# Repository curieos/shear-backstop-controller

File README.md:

# Shear Backstop Controller
A shear backstop controller running on a Teensy 3.5 with AMIS30543 stepper drivers and an Adafruit TFT LCD

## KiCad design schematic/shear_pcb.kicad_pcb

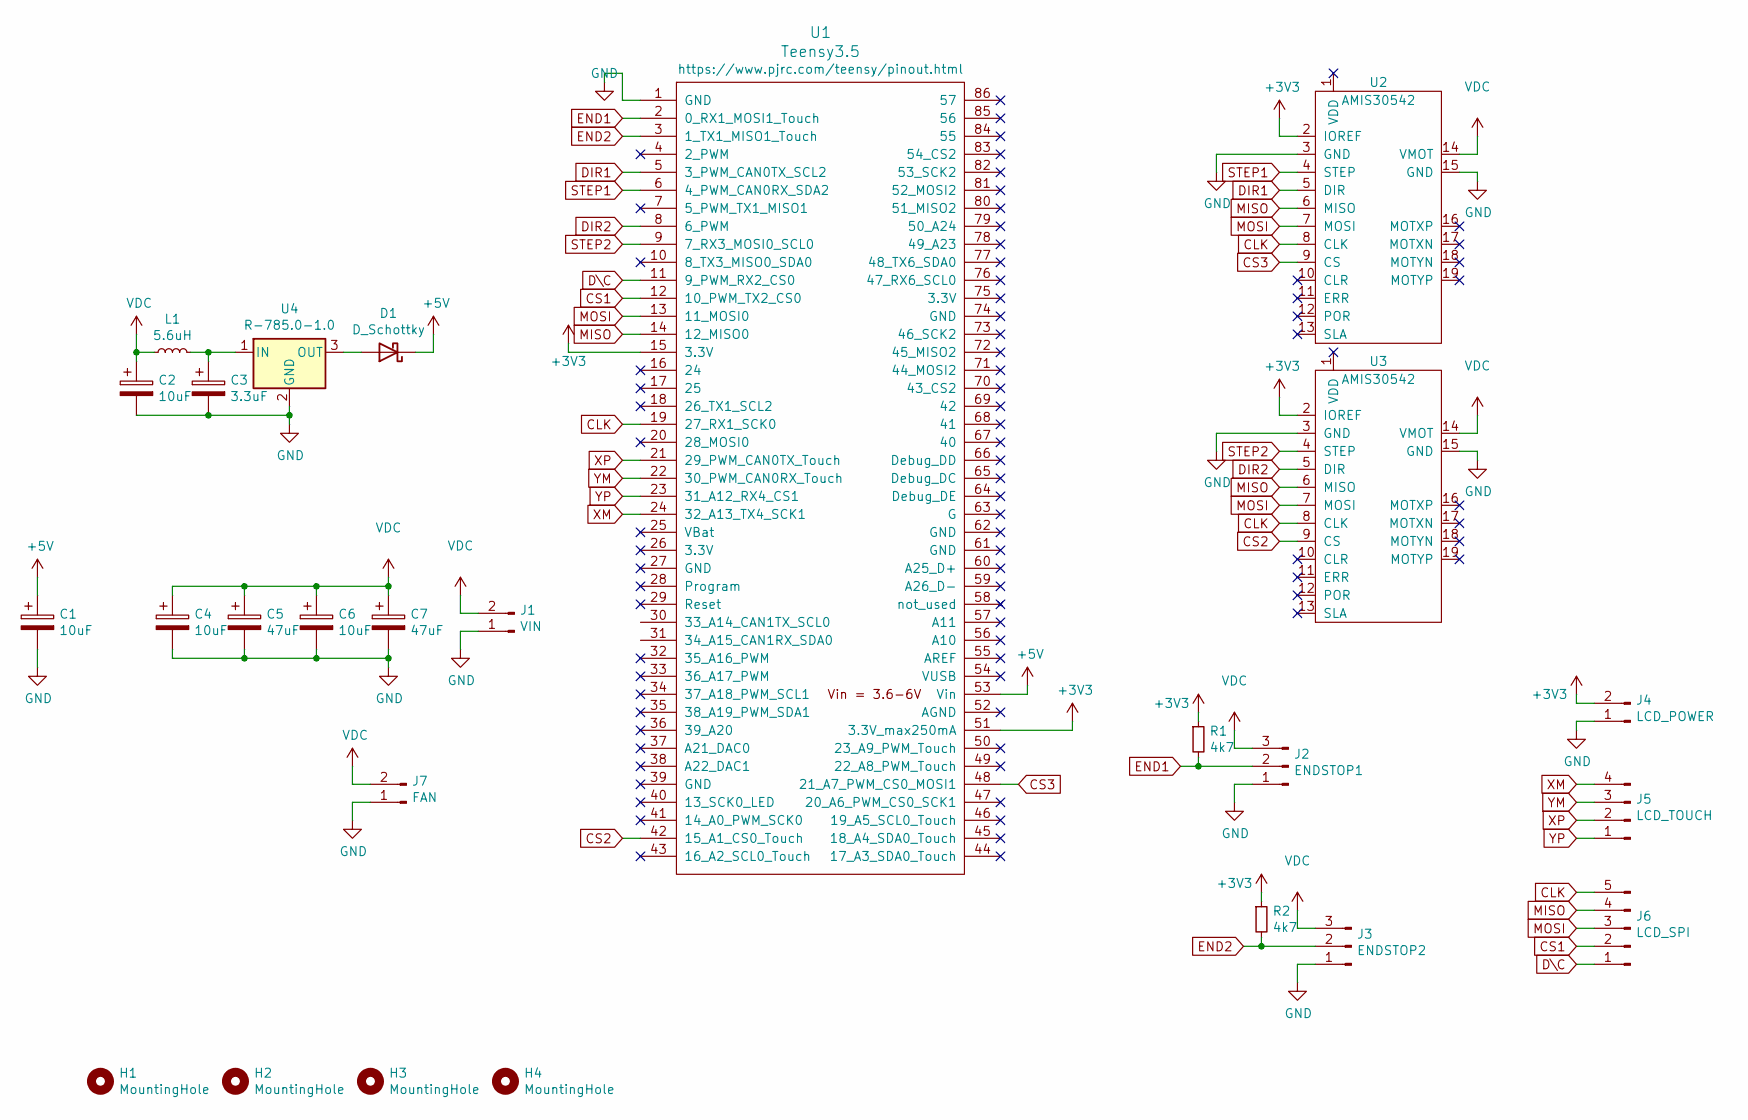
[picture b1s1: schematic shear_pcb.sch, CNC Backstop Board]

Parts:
C1: 10uF; C_1206_3216Metric_Pad1.42x1.75mm_HandSolder
C2: 10uF; C_1210_3225Metric_Pad1.42x2.65mm_HandSolder
C3: 3.3uF; C_1210_3225Metric_Pad1.42x2.65mm_HandSolder
C4, C6: 10uF; CP_Elec_6.3x3
C5, C7: 47uF; CP_Elec_6.3x3
D1: D_Schottky; D_0805_2012Metric_Pad1.15x1.40mm_HandSolder
H1, H2, H3, H4: MountingHole; MountingHole_3.2mm_M3_ISO7380
J1: VIN; TerminalBlock_bornier-2_P5.08mm
J2: ENDSTOP1; PinHeader_1x03_P2.54mm_Vertical
J3: ENDSTOP2; PinHeader_1x03_P2.54mm_Vertical
J4: LCD_POWER; PinHeader_1x02_P2.54mm_Vertical
J5: LCD_TOUCH; PinHeader_1x04_P2.54mm_Vertical
J6: LCD_SPI; PinHeader_1x05_P2.54mm_Vertical
J7: FAN; JST_EH_B2B-EH-A_1x02_P2.50mm_Vertical
L1: 5.6uH; L_Bourns-SRN4018
R1, R2: 4k7; R_0805_2012Metric_Pad1.15x1.40mm_HandSolder
U1: Teensy3.5; Teensy35_36
U2, U3: AMIS30542
U4: R-785.0-1.0; Converter_DCDC_RECOM_R-78E-0.5_THT

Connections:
+3V3: J4.2, R1.1, R2.1, U1.15 (3.3V), U1.51 (3.3V_max250mA), U2.2 (IOREF), U3.2 (IOREF)
+5V: C1.1, D1.1 (K), U1.53 (Vin)
CLK: J6.5, U1.19 (27_RX1_SCK0), U2.8 (CLK), U3.8 (CLK)
CS1: J6.2, U1.12 (10_PWM_TX2_CS0)
CS2: U1.42 (15_A1_CS0_Touch), U3.9 (CS)
CS3: U1.48 (21_A7_PWM_CS0_MOSI1), U2.9 (CS)
DIR1: U1.5 (3_PWM_CAN0TX_SCL2), U2.5 (DIR)
DIR2: U1.8 (6_PWM), U3.5 (DIR)
D\C: J6.1, U1.11 (9_PWM_RX2_CS0)
END1: J2.2, R1.2, U1.2 (0_RX1_MOSI1_Touch)
END2: J3.2, R2.2, U1.3 (1_TX1_MISO1_Touch)
GND: C1.2, C2.2, C3.2, C4.2, C5.2, C6.2, C7.2, J1.1, J2.1, J3.1, J4.1, J7.1, U1.1 (GND), U2.3 (GND), U2.15 (GND), U3.3 (GND), U3.15 (GND), U4.2 (GND)
MISO: J6.4, U1.14 (12_MISO0), U2.6 (MISO), U3.6 (MISO)
MOSI: J6.3, U1.13 (11_MOSI0), U2.7 (MOSI), U3.7 (MOSI)
unnamed: C3.1, L1.2, U4.1 (IN)
unnamed: D1.2 (A), U4.3 (OUT)
STEP1: U1.6 (4_PWM_CAN0RX_SDA2), U2.4 (STEP)
STEP2: U1.9 (7_RX3_MOSI0_SCL0), U3.4 (STEP)
VDC: C2.1, C4.1, C5.1, C6.1, C7.1, J1.2, J2.3, J3.3, J7.2, L1.1, U2.14 (VMOT), U3.14 (VMOT)
XM: J5.4, U1.24 (32_A13_TX4_SCK1)
XP: J5.2, U1.21 (29_PWM_CAN0TX_Touch)
YM: J5.3, U1.22 (30_PWM_CAN0RX_Touch)
YP: J5.1, U1.23 (31_A12_RX4_CS1)

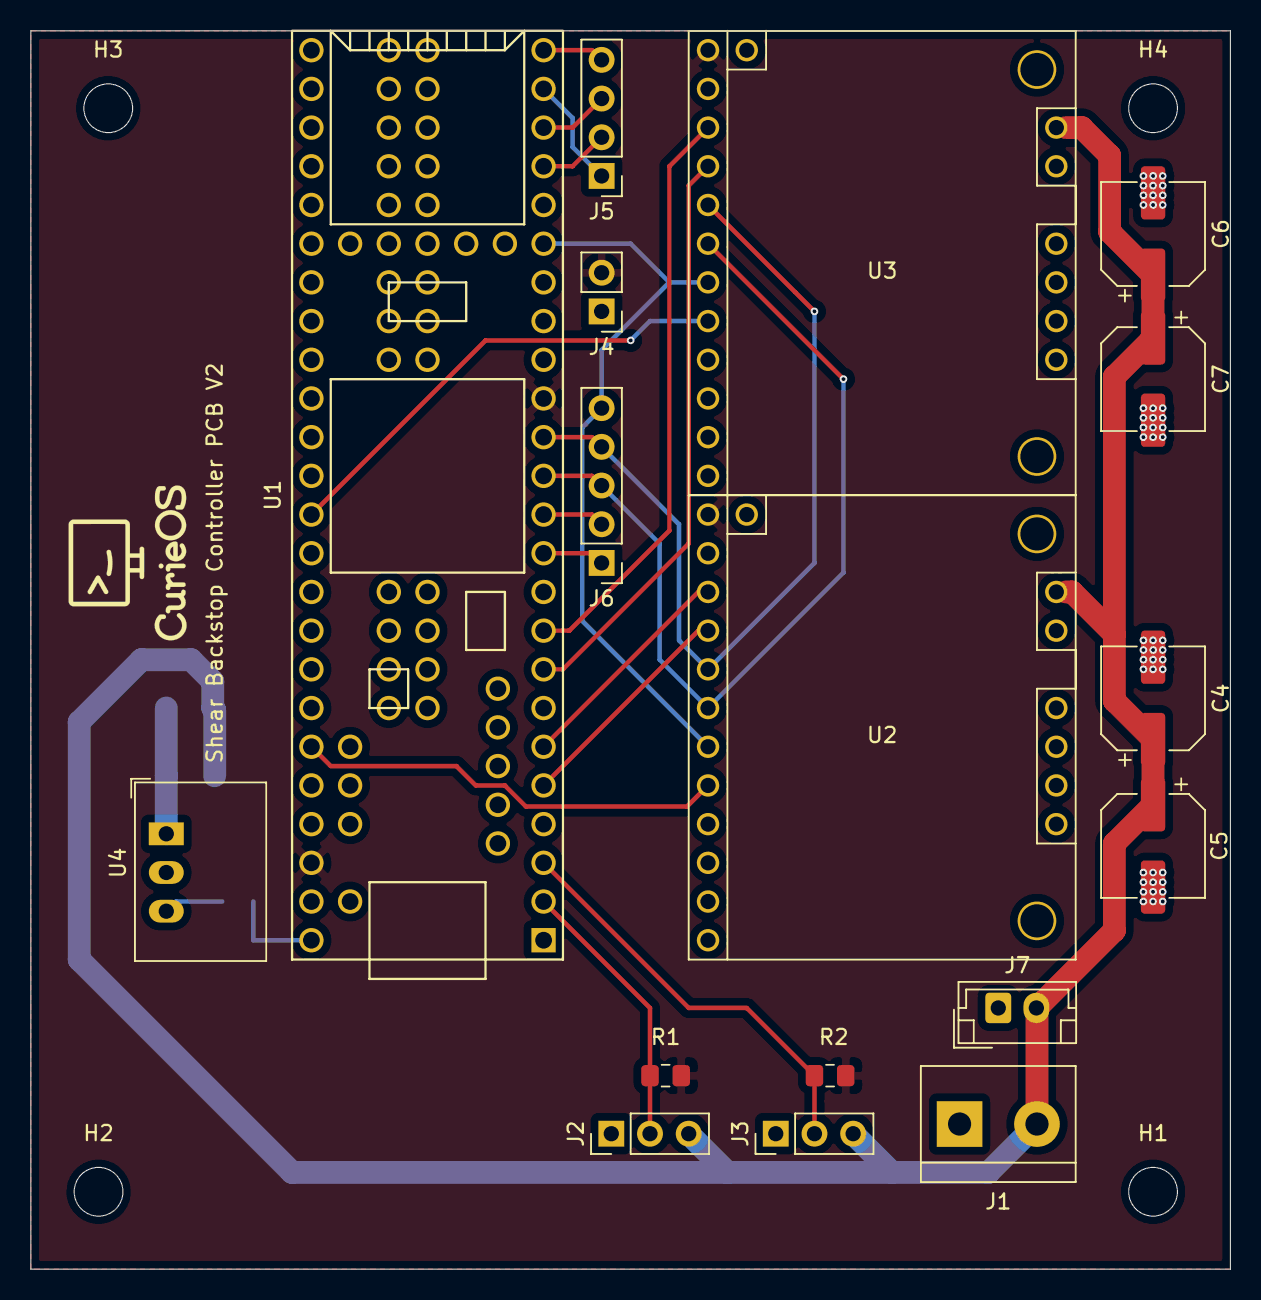
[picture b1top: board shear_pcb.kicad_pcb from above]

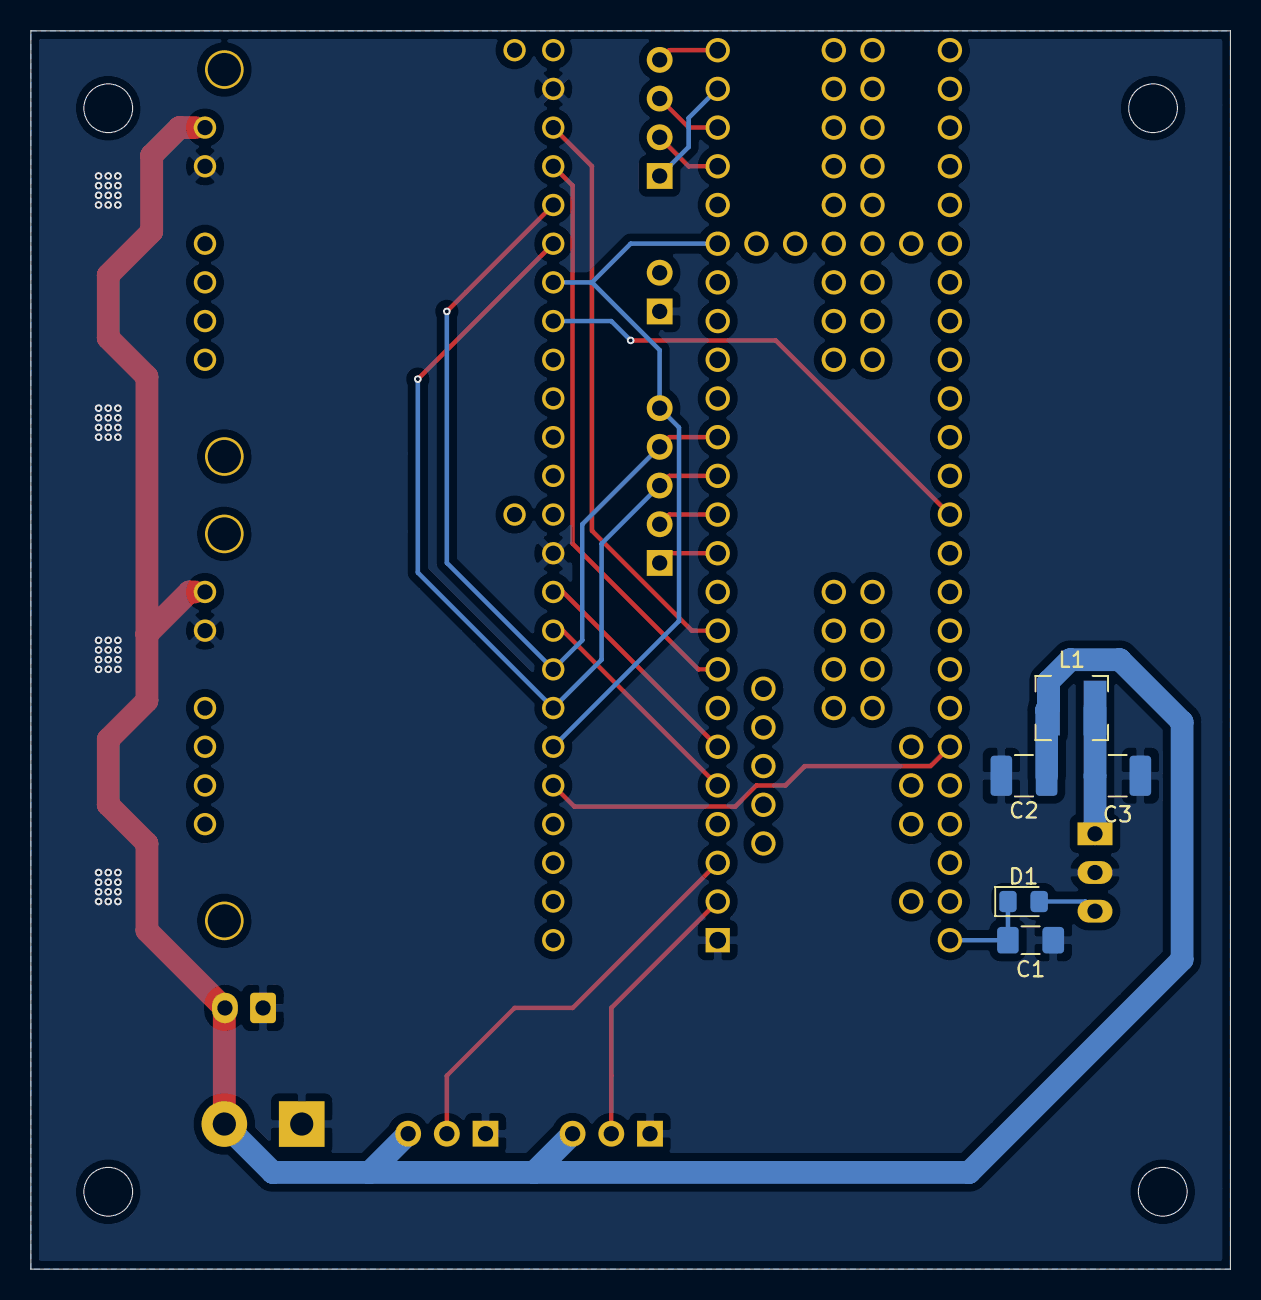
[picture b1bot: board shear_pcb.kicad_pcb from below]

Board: 2 copper layers, 78.7 x 81.3 mm, 26 parts (5 on the bottom side), 23 nets.

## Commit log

2019-04-19 Add initialized Platform.io project
2019-05-02 Update .ini file with correct LCD includes for this project
2019-05-02 Add Machine class files
2019-05-02 Move PIO project to code directory
2019-05-02 Add KiCAD project
2019-05-02 Add Teensy 3.5 to schematic
2019-05-03 Add AMIS30542 schematic
2019-05-03 Add AMIS30542 footprint
2019-05-03 Add AMIS30542 linaries
2019-05-03 Add components to schematic
    -2x AMIS30542
2019-05-03 Generate Netlist
2019-05-03 Generated simple PCB
    Needs additional components, etc.
2019-05-03 Edit AMIS pins to be bidirectional
2019-05-03 Connect AMIS drives to Teensy MCU
2019-05-03 Fix missing pin on AMIS
2019-05-03 Add connectors and first pcb design
2019-05-07 Setup for PIO unit testing
2019-05-09 Redesign PCB for single-side fabrication
    -Add power and endstop connectors
    -Add LCD connector
    -Reroute SPI and step/dir tracks
2019-05-24 Update repo in preparation for new computer
2019-05-28 Switch over to VSCode. Add required files
2019-05-28 Update file headers with new header generator
2019-07-11 Add recommended vscode extension
2019-07-11 Update schematic with modified pinouts
2019-07-11 Add config values for the LCD and stepper drivers
2019-07-11 Create an LCD class for controlling the touch LCD
2019-07-11 Add LCD object to control object
2019-07-11 Move stepper driver initalization to separate func
2019-07-11 Change header blocks to match other files
2019-07-11 Add code to initialize the machine and controller
2019-07-16 Add basic keypad display to LCD
2020-08-20 Rework circuit board
2020-08-22 Updated capacitor footprints
2020-08-22 Add CurieOS Logo to board
2020-08-25 Rebuild board based on feedback
2020-08-31 Add step file for CAD work
2020-09-10 Latest stable board and firmware
